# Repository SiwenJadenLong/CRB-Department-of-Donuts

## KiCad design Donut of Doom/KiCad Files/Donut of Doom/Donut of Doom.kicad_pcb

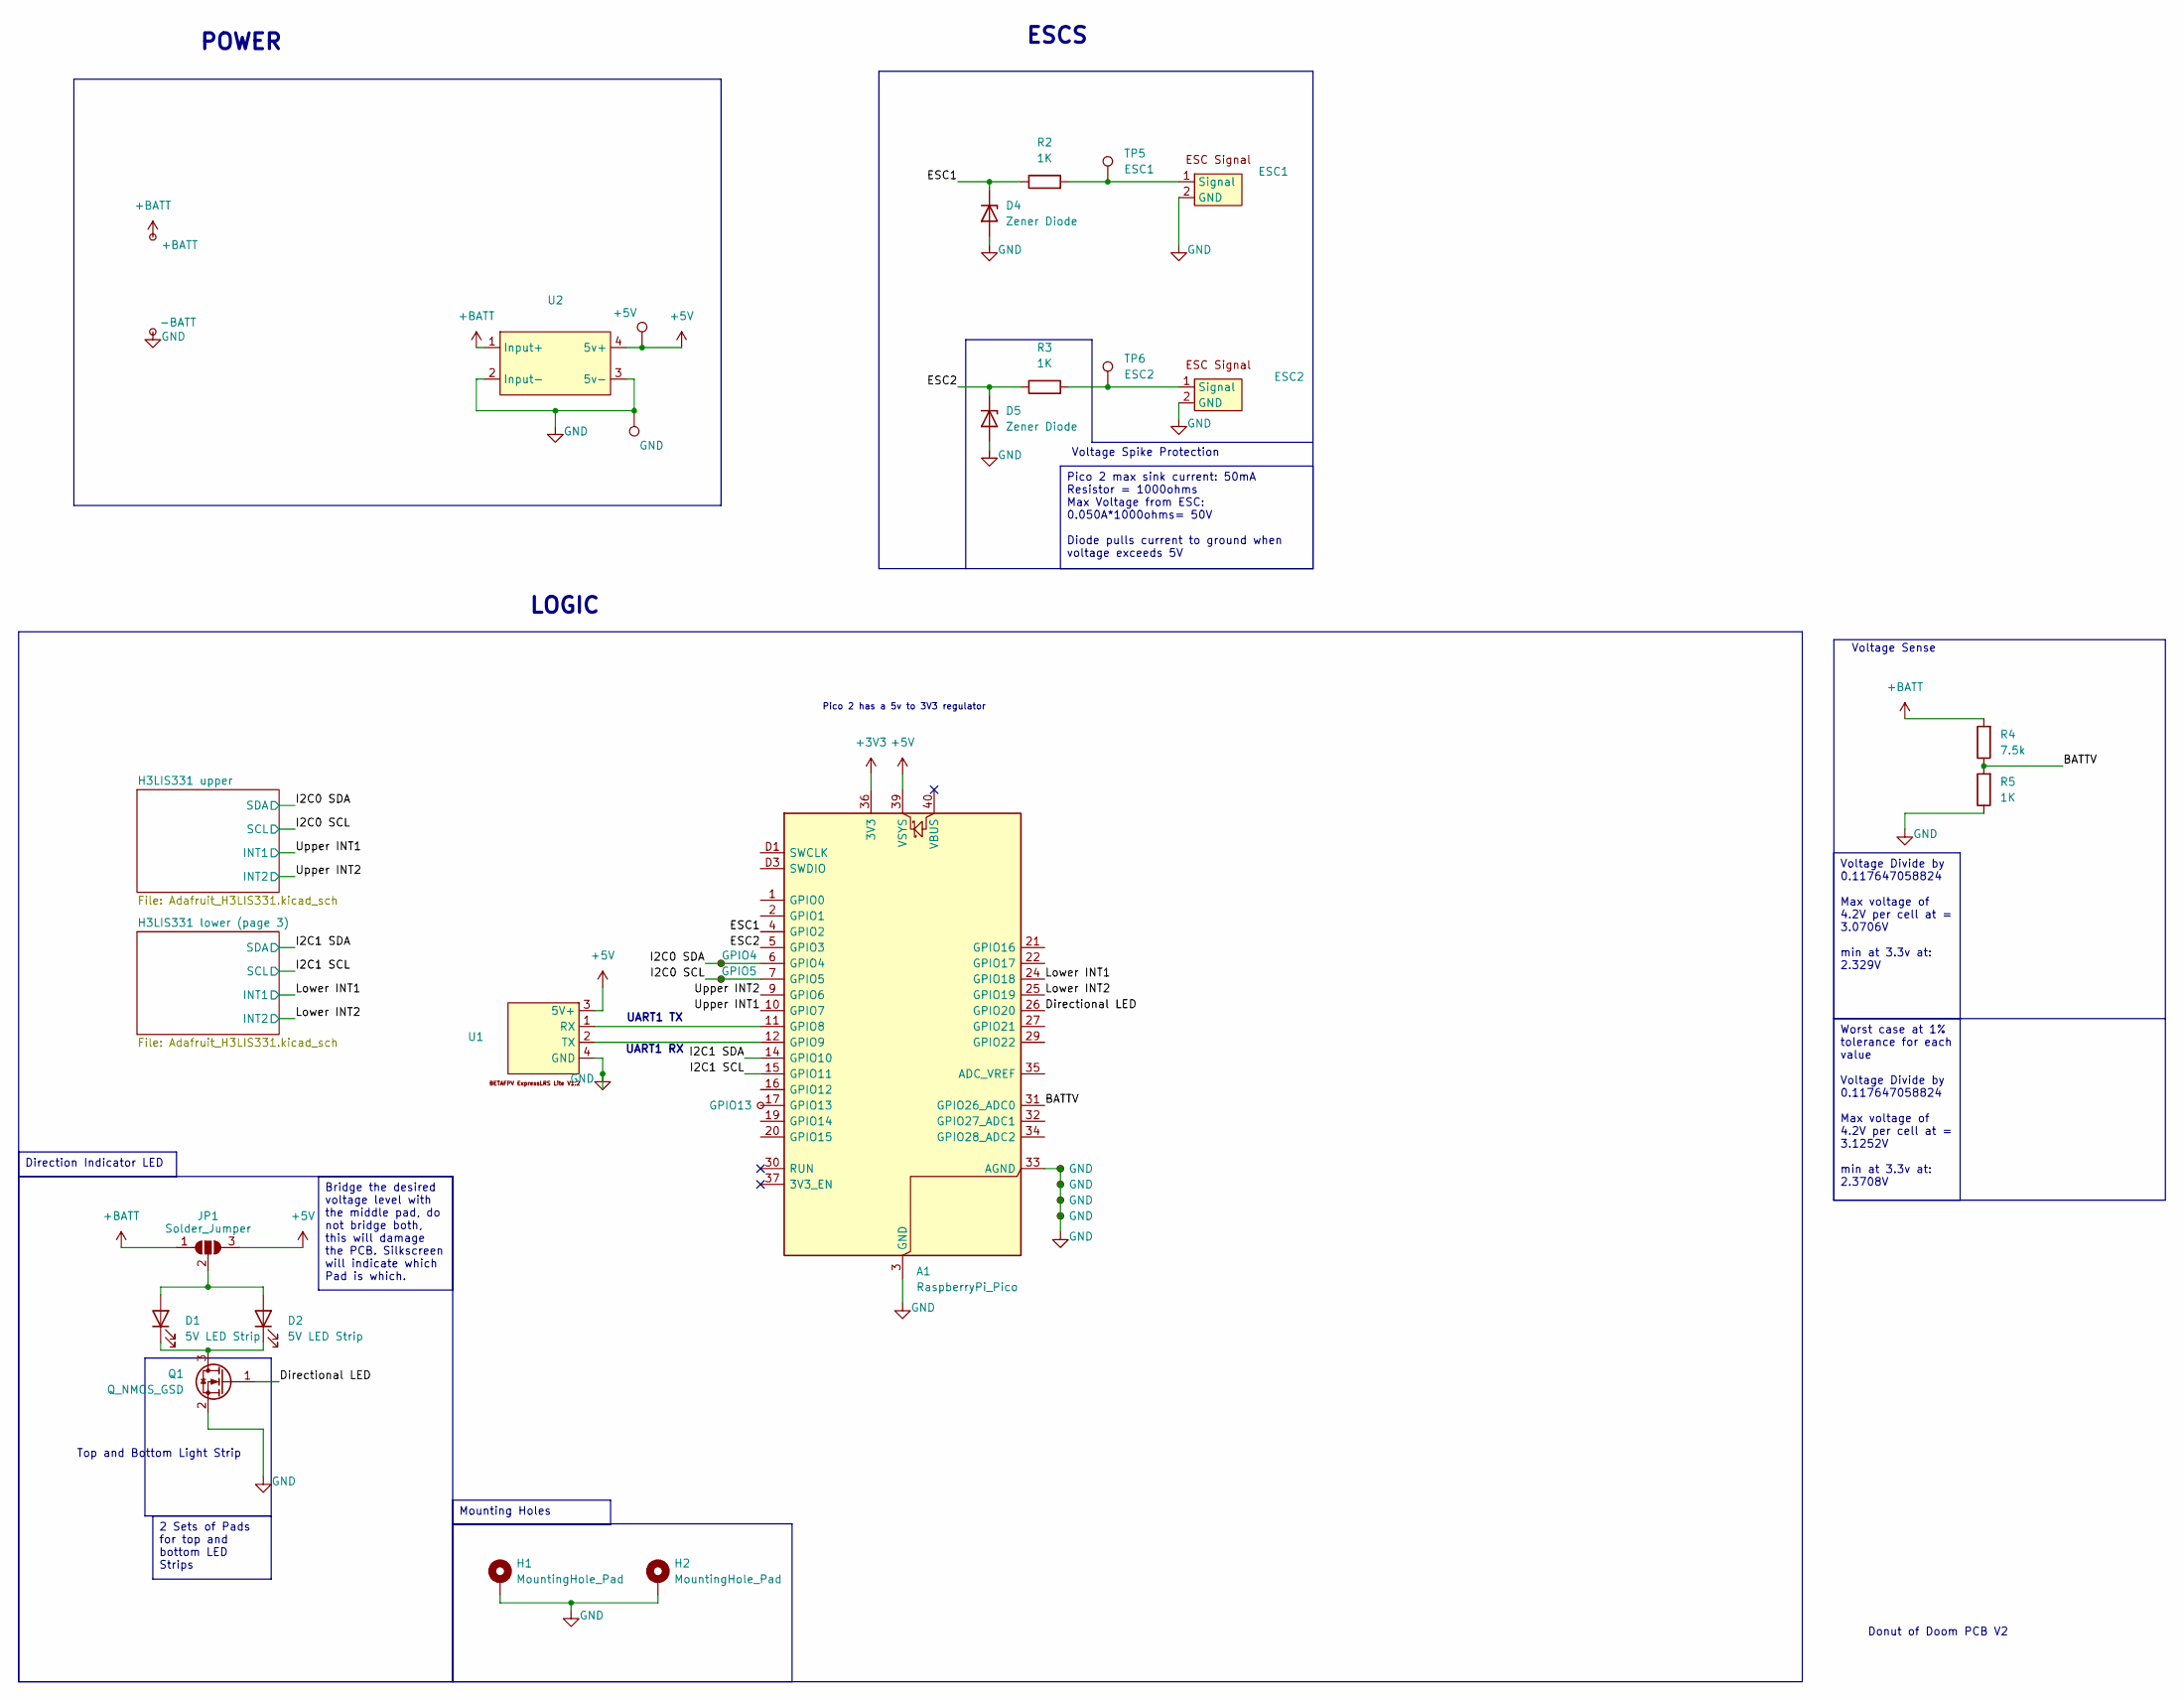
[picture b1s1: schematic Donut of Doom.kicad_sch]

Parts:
A1: RaspberryPi_Pico; RaspberryPi_Pico_Original_SMD_HandSolder
D1, D2: 5V LED Strip; 2 pth Pads
D4, D5: Zener Diode; SGP1610N2
ESC1, ESC2: 2_2mmx1.5mm_smd_pad
EX1: GPIO4; Pico_pth_pad
EX2: GPIO5; Pico_pth_pad
EX5: GPIO13; Pico_pth_pad
EX8, EX9, EX11, EX12: GND; Pico_pth_GND
H1, H2: MountingHole_Pad; MountingHole_2.2mm_M2_DIN965_Pad
JP1: Solder_Jumper; SolderJumper-3_P1.3mm_Open_RoundedPad1.0x1.5mm_NumberLabels
Q1: Q_NMOS_GSD; TSOT-23
R2, R3, R5: 1K; R_0603_1608Metric_Pad0.98x0.95mm_HandSolder
R4: 7.5k; R_0603_1608Metric_Pad0.98x0.95mm_HandSolder
TP1: +BATT; 3.5mmx2.5mm_oval_smd_pad
TP2: -BATT; 3.5mmx2.5mm_oval_smd_pad
TP3: GND; TestPoint_Pad_D3.0mm
TP4: +5V; TestPoint_Pad_D2.0mm
TP5: ESC1; TestPoint_Pad_D1.5mm
TP6: ESC2; TestPoint_Pad_D1.5mm
U1: BetaFPV ExpressLRS Reciever Lite V1.2
U2: 5V_Stepdown_module

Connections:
+3V3: A1.36 (3V3); also elsewhere on the board
+5V: A1.39 (VSYS), JP1.3 (B), TP4.1 (1_1), U1.3 (5V+), U2.4 (5v+)
+BATT: JP1.1 (A), R4.2, TP1.1 (1_1), U2.1 (Input+)
/BATTV: A1.31 (GPIO26_ADC0), R4.1, R5.2
/Directional LED: A1.26 (GPIO20), Q1.1 (G)
/ESC1: A1.4 (GPIO2), D4.1 (K), R2.1
/ESC2: A1.5 (GPIO3), D5.1 (K), R3.1
/I2C0 SCL: A1.7 (GPIO5), EX2.1 (1_1); also elsewhere on the board
/I2C0 SDA: A1.6 (GPIO4), EX1.1 (1_1); also elsewhere on the board
/I2C1 SCL: A1.15 (GPIO11); also elsewhere on the board
/I2C1 SDA: A1.14 (GPIO10); also elsewhere on the board
/Lower INT1: A1.24 (GPIO18); also elsewhere on the board
/Lower INT2: A1.25 (GPIO19); also elsewhere on the board
/Upper INT1: A1.10 (GPIO7); also elsewhere on the board
/Upper INT2: A1.9 (GPIO6); also elsewhere on the board
GND: A1.3 (GND), A1.8 (GND), A1.13 (GND), A1.18 (GND), A1.23 (GND), A1.28 (GND), A1.33 (AGND), A1.38 (GND), A1.D2 (GND), D4.2 (A), D5.2 (A), ESC1.2 (GND), ESC2.2 (GND), EX8.1 (1_1), EX9.1 (1_1), EX11.1 (1_1), EX12.1 (1_1), H1.1 (1_1), H2.1, Q1.2 (S), R5.1, TP2.1 (1_1), TP3.1 (1_1), U1.4 (GND), U2.2 (Input-), U2.3 (5v-); also elsewhere on the board
unnamed: A1.11 (GPIO8), U1.1 (RX)
unnamed: A1.12 (GPIO9), U1.2 (TX)
unnamed: A1.17 (GPIO13), EX5.1 (1_1)
unnamed: D1.2 (A), D2.2 (A), JP1.2 (C)
unnamed: D1.1 (K), D2.1 (K), Q1.3 (D)
unnamed: ESC1.1 (Signal), R2.2, TP5.1 (1_1)
unnamed: ESC2.1 (Signal), R3.2, TP6.1 (1_1)

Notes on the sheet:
Voltage Spike Protection
LOGIC
ESCS
UART1 RX
POWER
Pico 2 has a 5v to 3V3 regulator
Voltage Sense
Donut of Doom PCB V2
Top and Bottom Light Strip
UART1 TX
Pico 2 max sink current: 50mA Resistor = 1000ohms Max Voltage from ESC: 0.050A*1000ohms= 50V Diode pulls current to ground when voltage exceeds 5V
Worst case at 1% tolerance for each value Voltage Divide by 0.117647058824 Max voltage of 4.2V per cell at = 3.1252V min at 3.3v at: 2.3708V
Direction Indicator LED
Mounting Holes
Bridge the desired voltage level with the middle pad, do not bridge both, this will damage the PCB. Silkscreen will indicate which Pad is which.
2 Sets of Pads for top and bottom LED Strips
Voltage Divide by 0.117647058824 Max voltage of 4.2V per cell at = 3.0706V min at 3.3v at: 2.329V

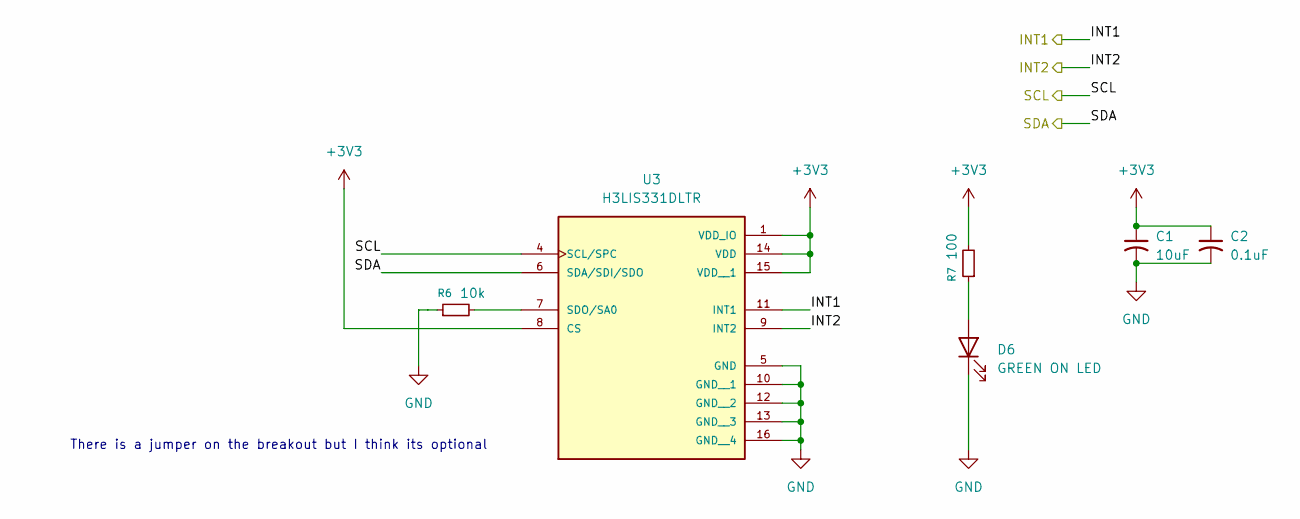
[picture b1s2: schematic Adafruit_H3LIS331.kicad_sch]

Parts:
C1: 10uF; C_0805_2012Metric_Pad1.18x1.45mm_HandSolder
C2: 0.1uF; C_0603_1608Metric_Pad1.08x0.95mm_HandSolder
D6: GREEN ON LED; LED_0603_1608Metric_Pad1.05x0.95mm_HandSolder
R6: 10k; R_0603_1608Metric_Pad0.98x0.95mm_HandSolder
R7: 100; R_0603_1608Metric_Pad0.98x0.95mm_HandSolder
U3: H3LIS331DLTR; LGA-16_3x3mm_P0.5mm_LayoutBorder3x5y

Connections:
+3V3: C1.1, C2.1, R7.2, U3.1 (VDD_IO), U3.8 (CS), U3.14 (VDD), U3.15 (VDD__1); also elsewhere on the board
/I2C0 SCL: U3.4 (SCL/SPC); also elsewhere on the board
/I2C0 SDA: U3.6 (SDA/SDI/SDO); also elsewhere on the board
/Upper INT1: U3.11 (INT1); also elsewhere on the board
/Upper INT2: U3.9 (INT2); also elsewhere on the board
GND: C1.2, C2.2, D6.1 (K), R6.1, U3.5 (GND), U3.10 (GND__1), U3.12 (GND__2), U3.13 (GND__3), U3.16 (GND__4); also elsewhere on the board
unnamed: D6.2 (A), R7.1
unnamed: R6.2, U3.7 (SDO/SA0)

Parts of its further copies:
C3: 10uF; C_0805_2012Metric_Pad1.18x1.45mm_HandSolder
C4: 0.1uF; C_0603_1608Metric_Pad1.08x0.95mm_HandSolder
D7: GREEN ON LED; LED_0603_1608Metric_Pad1.05x0.95mm_HandSolder
R8: 10k; R_0603_1608Metric_Pad0.98x0.95mm_HandSolder
R9: 100; R_0603_1608Metric_Pad0.98x0.95mm_HandSolder
U4: H3LIS331DLTR; LGA-16_3x3mm_P0.5mm_LayoutBorder3x5y

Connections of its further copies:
+3V3: C3.1, C4.1, R9.2, U4.1 (VDD_IO), U4.8 (CS), U4.14 (VDD), U4.15 (VDD__1); also elsewhere on the board
/I2C1 SCL: U4.4 (SCL/SPC); also elsewhere on the board
/I2C1 SDA: U4.6 (SDA/SDI/SDO); also elsewhere on the board
/Lower INT1: U4.11 (INT1); also elsewhere on the board
/Lower INT2: U4.9 (INT2); also elsewhere on the board
GND: C3.2, C4.2, D7.1 (K), R8.1, U4.5 (GND), U4.10 (GND__1), U4.12 (GND__2), U4.13 (GND__3), U4.16 (GND__4); also elsewhere on the board
unnamed: D7.2 (A), R9.1
unnamed: R8.2, U4.7 (SDO/SA0)

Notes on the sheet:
There is a jumper on the breakout but I think its optional

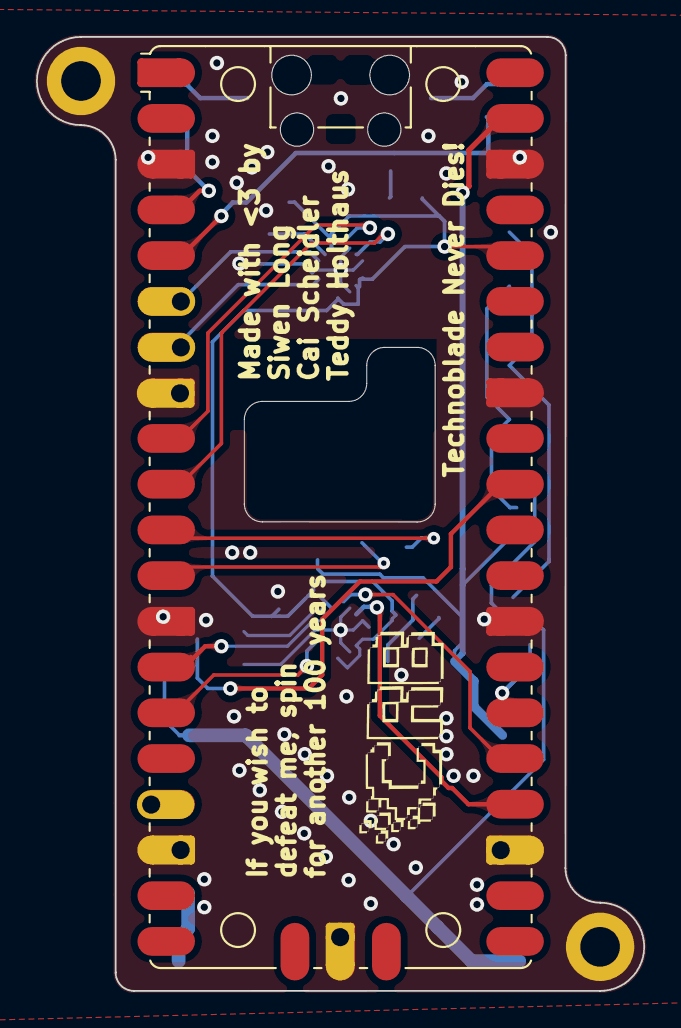
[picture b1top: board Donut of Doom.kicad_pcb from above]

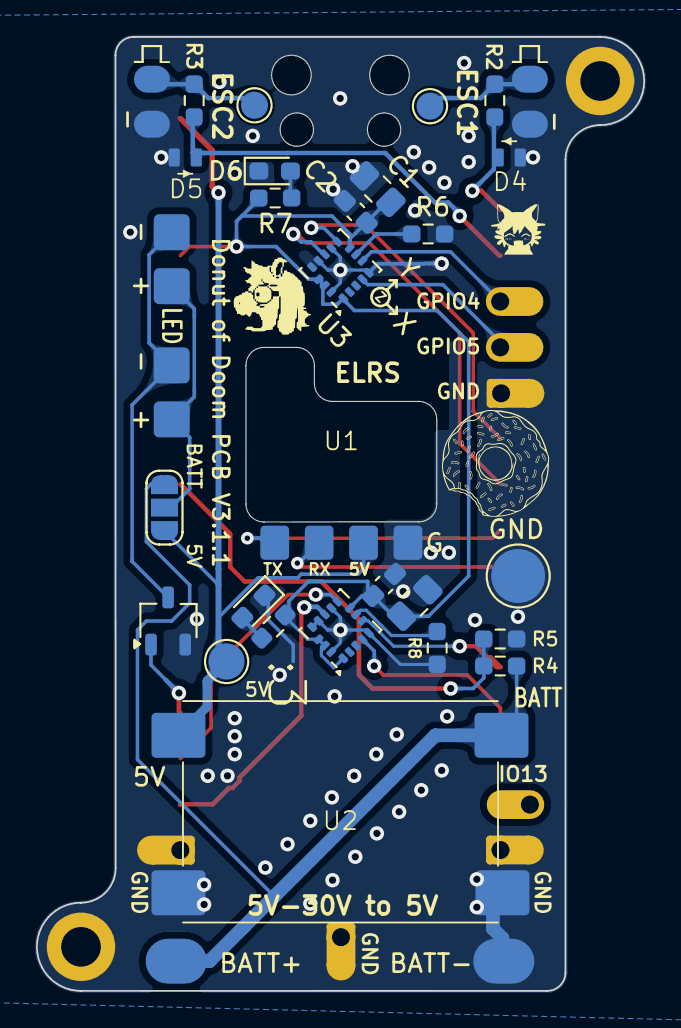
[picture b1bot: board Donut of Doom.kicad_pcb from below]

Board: 2 copper layers, 33.7 x 53.0 mm, 42 parts (32 on the bottom side), 27 nets.

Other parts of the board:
H1#2: MountingHole_Pad; MountingHole_2.2mm_M2_DIN965_Pad

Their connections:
GND: H1#2.1 (1_1); also elsewhere on the board

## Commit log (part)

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2025-09-25 created schematic project
2025-09-25 rearranged folders
2025-09-27 open melt2 code is here
2025-09-29 ITS WORKING
    BUT TO GET IT TO COMPILE I HAD TO CHANGE THE NAME OF OPEN_DRAIN at "C:\Users\CAIS\Documents\Arduino\libraries\arduino-esp32-master\cores\esp32\esp32-hal-gpio.c" and "C:\Users\CAIS\Documents\Arduino\l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
2025-09-30 Switched to FIXED_PWM_THROTTLE
2025-10-03 robot should be able to move forward and also spin poorly with one wheel to turn
2025-10-07 Added Custom Symbol Library and worked more on Schematic
2025-10-18 GETTING STUCK IN THROTTLE/RC LOOP EVEN THOUGH BOTH ARE VALID, ACCELEROMETER IS NOT CONNECTING PROPERLY
2025-10-19 Motor is spinning when throttle is increased only when ESP32 is on but ESP32 says it is waiting for the RC to come online which makes no sense because then how is the motor receiver the transmitter's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
2025-10-19 Motor is spinning when throttle is increased only when ESP32 is on but ESP32 says it is waiting for the RC to come online which makes no sense because then how is the motor receiving the transmitter'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
2025-11-01 NEED to rewrite code to use esp32 servo library to change
2025-11-01 melty code rewrite
2025-11-01 Code update
2025-11-02 melty code working maybe need to make sure motor doesn't explode
2025-11-02 ITS WORKING THE MOTOR DIDN'T BLOW UP
2025-11-06 TEST THIS - throttle failsafe if transmitters turns off
2025-11-07 ts is not working
2025-11-07 killswitch implemented
2025-11-10 channels and colors for receiver connections added
2025-11-12 frequency changed to 60 because it should be at 60
2025-11-14 CODE SHOULD BE WORKING NOW, PULSE WIDTH SEEMS TO BE A 5 BIT NUMBER FOR SOME REASON
2025-11-15 accel_mount_radius is set where?
2025-11-15 ACCELEROMETER AXIS MAY HAVE BEEN INCORRECT
2025-11-15 changed default zero accel g offset to 2 from 1.5
2025-11-15 trygin to go solid when spinning up
2025-11-15 changed min translation rpm back to 200
2025-11-16 Super Donut of Doom is coming...
2025-11-28 Started a lot of work on DOD V2 PCB with the Pico 2
2025-11-28 Added voltage spike protection circuitry to ESCs
2025-11-29 fixed accel pins
2025-12-02 Made draft pcb for Plant Donut V2
2025-12-02 debug resistor and led finalized, export tested for dfm
2025-12-22 BEGINNING OF AUTOMELTY
2025-12-23 auto melty brain sim is coming along
2025-12-23 AutoMelty Brain Sim needs fixing but its getting there
2025-12-23 AMB To-do created
2025-12-24 melty brain is melting brain
2025-12-24 more progress on AMS
2025-12-24 run away not done
2026-01-15 New footprints for buck and accel, layout partially done.
2026-01-17 PCB almost finalized, awaiting dfm
2026-01-18 Finalized V1 Order, DFM completed
2026-01-31 fixed resistor values
2026-02-01 Added more breakouts, corrected MOSFET, better esc and led pads.
2026-02-01 Added better GND connections and Labels
2026-03-24 Turned accelorometer 45 degrees, increased clearence on elrs reciever
2026-03-24 Added 2nd accel, fixed mosfet, added more GND pads
2026-03-24 small silkscreen fixes
2026-03-25 added teardrops
2026-03-25 fixed lower accelerameter routing
2026-03-25 fixed dead copper
2026-06-29 V3 First rev finished
